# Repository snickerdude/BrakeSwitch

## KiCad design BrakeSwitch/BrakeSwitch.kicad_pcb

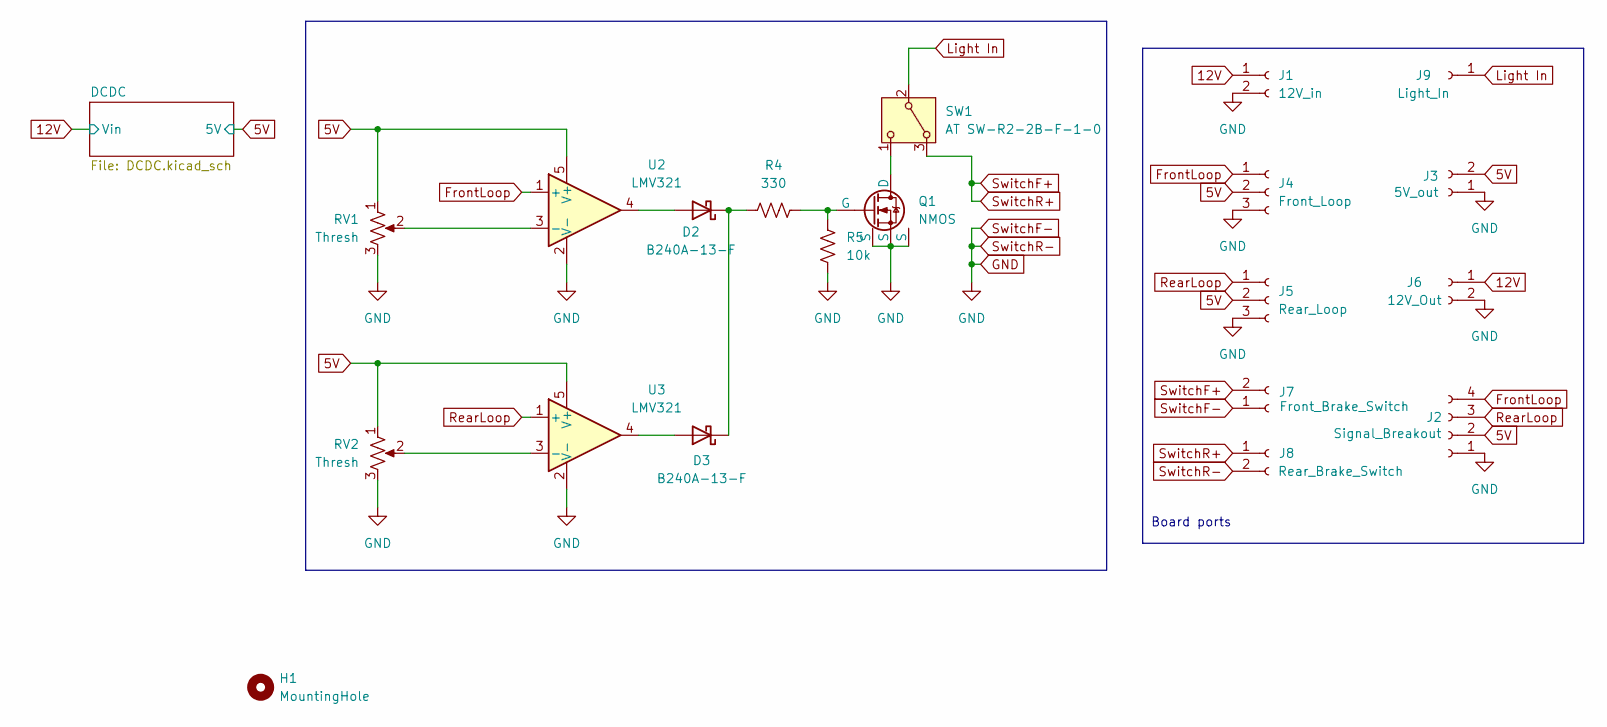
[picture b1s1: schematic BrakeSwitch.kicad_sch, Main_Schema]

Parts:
D2, D3: B240A-13-F; D_SMA
H1: MountingHole; MountingHole_6.5mm_Pad
J1: 12V_in; SolderPad_01x02
J2: Signal_Breakout; SolderPad_01x04
J3: 5V_out; SolderPad_01x02
J4: Front_Loop; SolderPad_01x03
J5: Rear_Loop; SolderPad_01x03
J6: 12V_Out; SolderPad_01x02
J7: Front_Brake_Switch; SolderPad_01x02
J8: Rear_Brake_Switch; SolderPad_01x02
J9: Light_In; SolderPad_01x01
Q1: NMOS; Vishay_PowerPAK_1212-8_Single
R4: 330; R_0603_1608Metric
R5: 10k; R_0603_1608Metric
RV1, RV2: Thresh; Potentiometer_Runtron_RM-065_Vertical
SW1: AT SW-R2-2B-F-1-0; SPDT_PanelMount_Switch
U2, U3: LMV321; SOT-23-5

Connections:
5V: J2.2, J3.2, J4.2, J5.2, RV1.1, RV2.1, U2.5 (V+), U3.5 (V+); also elsewhere on the board
12V: J1.1, J6.1; also elsewhere on the board
FrontLoop: J2.4, J4.1, U2.1 (+)
GND: J1.2, J2.1, J3.1, J4.3, J5.3, J6.2, J7.1, J8.2, Q1.1 (S), Q1.2 (S), Q1.3 (S), R5.2, RV1.3, RV2.3, U2.2 (V-), U3.2 (V-); also elsewhere on the board
Light In: J9.1, SW1.2 (B)
unnamed: D2.2 (A), U2.4
unnamed: D2.1 (K), D3.1 (K), R4.1
unnamed: D3.2 (A), U3.4
unnamed: Q1.5 (D), SW1.1 (C)
unnamed: Q1.4 (G), R4.2, R5.1
unnamed: RV1.2, U2.3 (-)
unnamed: RV2.2, U3.3 (-)
RearLoop: J2.3, J5.1, U3.1 (+)
SwitchF+: J7.2, J8.1, SW1.3 (A)

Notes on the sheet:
Board ports

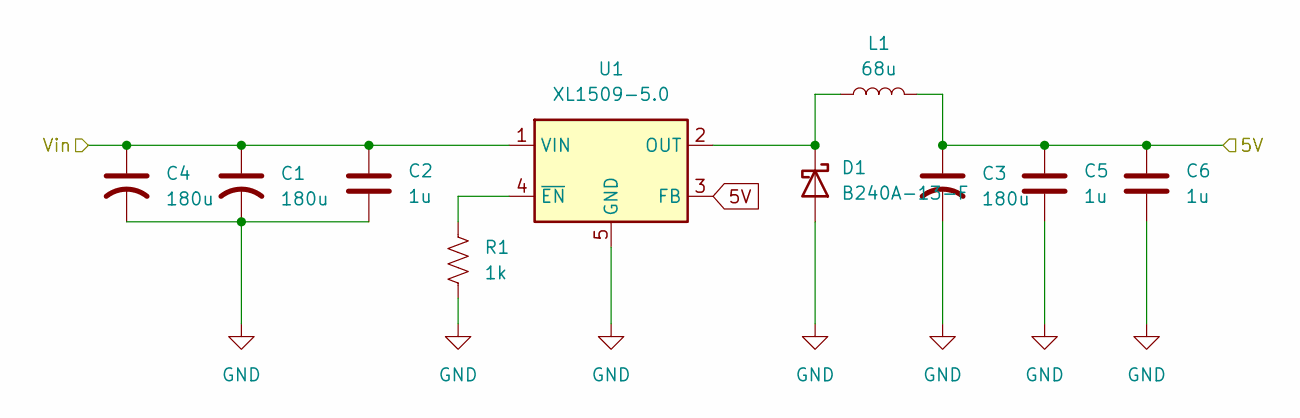
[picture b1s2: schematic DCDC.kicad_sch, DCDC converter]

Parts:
C1, C3, C4: 180u; CP_Elec_8x10.5
C2, C5, C6: 1u; C_0603_1608Metric_Pad1.08x0.95mm_HandSolder
D1: B240A-13-F; D_SMA
L1: 68u; L_12x12mm_H4.5mm
R1: 1k; R_0603_1608Metric
U1: XL1509-5.0; SOIC-8_3.9x4.9mm_P1.27mm

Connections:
5V: C3.1, C5.1, C6.1, L1.2, U1.3 (FB); also elsewhere on the board
12V: C1.1, C2.1, C4.1, U1.1 (VIN); also elsewhere on the board
GND: C1.2, C2.2, C3.2, C4.2, C5.2, C6.2, D1.2 (A), R1.2, U1.5 (GND), U1.6 (GND), U1.7 (GND), U1.8 (GND); also elsewhere on the board
unnamed: D1.1 (K), L1.1, U1.2 (OUT)
unnamed: R1.1, U1.4 (~EN)

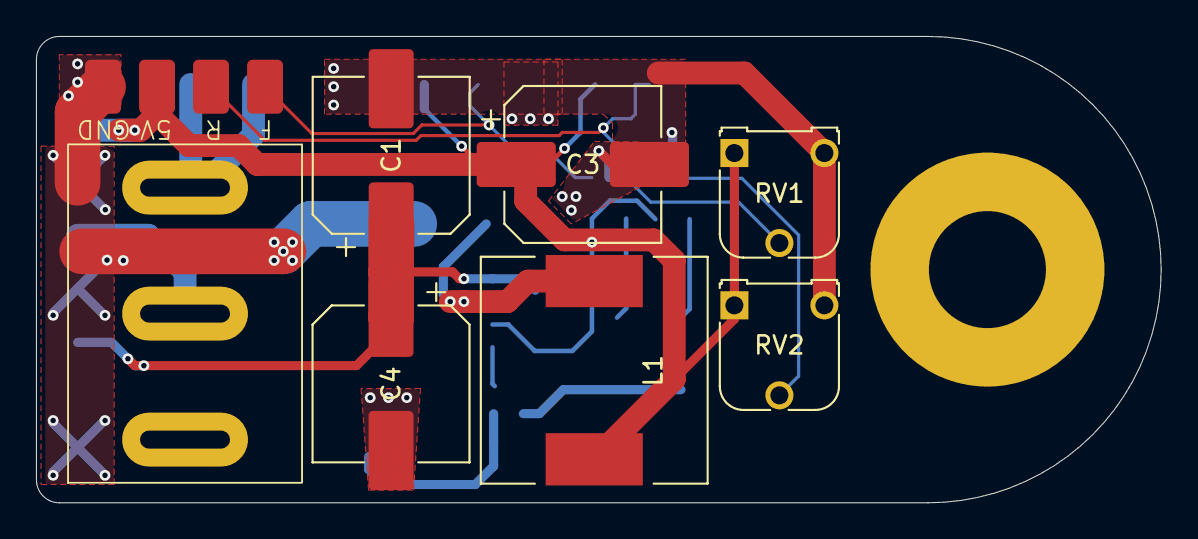
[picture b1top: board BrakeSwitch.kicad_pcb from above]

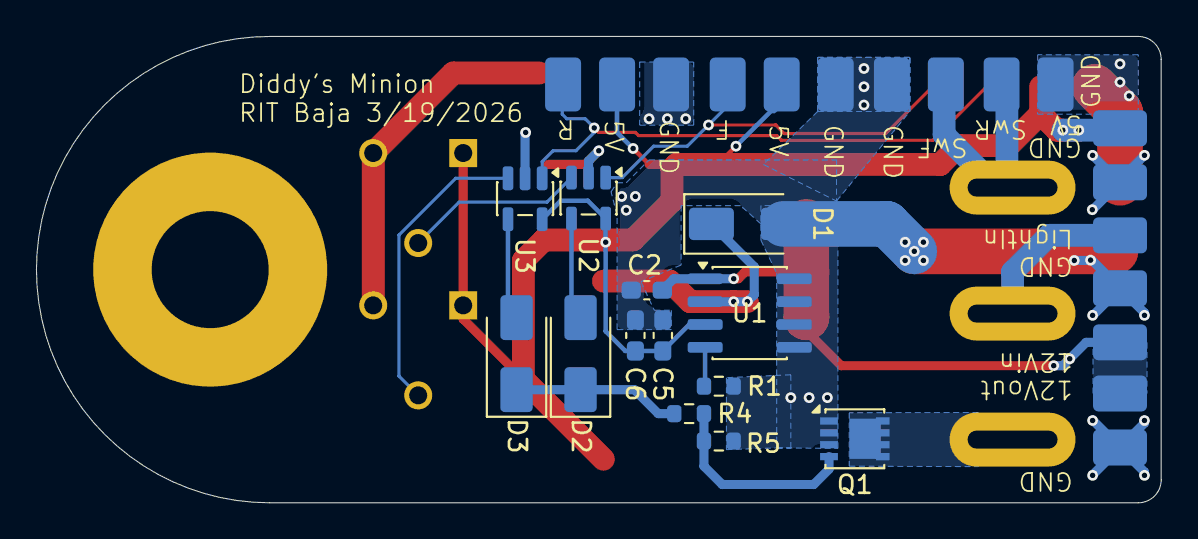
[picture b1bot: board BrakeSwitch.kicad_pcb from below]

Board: 2 copper layers, 62.5 x 25.9 mm, 30 parts (21 on the bottom side), 16 nets.

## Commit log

2026-03-18 Simulation added
2026-03-18 Initialize README with project description
2026-03-18 test commit
2026-03-18 removed test file
2026-03-18 initial kicad files
2026-03-18 Schematic first rev. Need to check light wiring
2026-03-18 Assigned most footprints
2026-03-18 progress save
2026-03-19 Desktop updated
2026-03-19 betime
2026-03-19 Basic layout done
2026-03-20 Some feedback and layout
2026-03-20 Laptop save
2026-03-24 deskptop progress save
2026-03-25 Layout doneish
2026-03-25 took some screenshots on my laptop
2026-03-26 Starting traces
2026-03-26 Finished tracing
2026-03-26 Done?
2026-03-26 Added 3d model for switch
2026-03-26 laptop closeout
2026-03-26 please
2026-03-26 added fab files
2026-03-26 fab files
